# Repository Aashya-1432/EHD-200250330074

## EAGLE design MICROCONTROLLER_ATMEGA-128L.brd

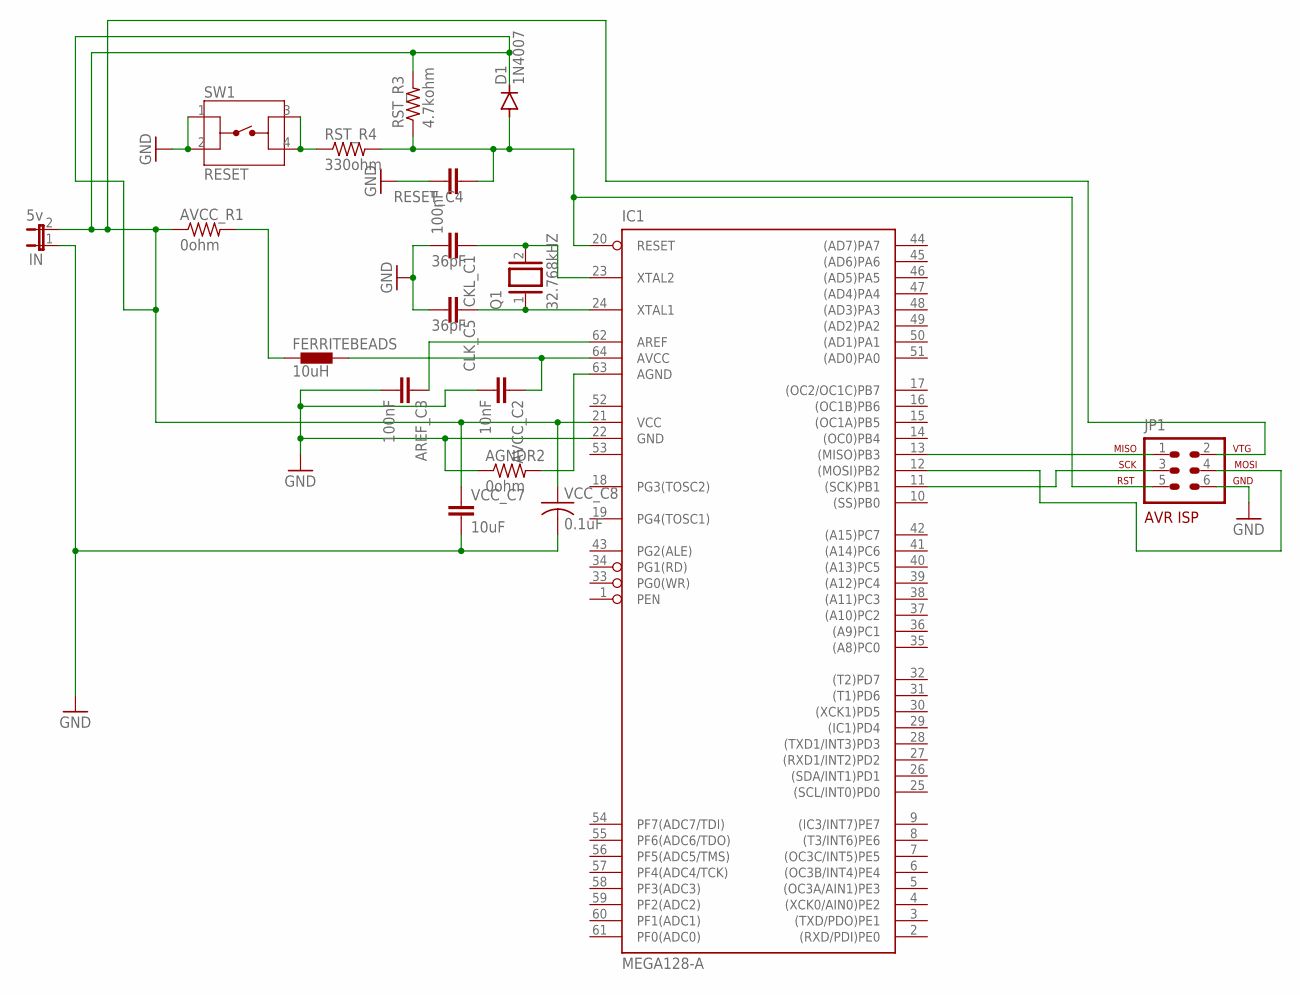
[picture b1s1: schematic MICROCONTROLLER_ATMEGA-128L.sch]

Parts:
AGNDR2: 0ohm; 0204/5
AREF_C3: 100nF; C5B3
AVCC_C2: 10nF; C5B3
AVCC_R1: 0ohm; 0204/5
CKL_C1: 36pF; C5B3
CLK_C5: 36pF; C5B3
D1: 1N4007; DO41-10
FERRITEBEADS: 10uH; 0402
IC1: MEGA128-A; TQFP64
IN: 5v; JP1
JP1: AVR-ISP-6R
Q1: 32.768kHZ; QS
RESET_C4: 100nF; C5B3
RST_R3: 4.7kohm; 0204/5
RST_R4: 330ohm; 0204/5
SW1: RESET; TE_FSM4JSMA
VCC_C7: 10uF; C5B3
VCC_C8: 0.1uF; C0603K

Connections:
GND: AGNDR2.1, AREF_C3.2, AVCC_C2.2, CKL_C1.2, CLK_C5.2, IC1.22 (GND), IN.1, JP1.6, RESET_C4.2, SW1.1, SW1.2, VCC_C7.2, VCC_C8.2
GND1: IC1.53 (GND1)
unnamed: RST_R4.1, SW1.3, SW1.4
unnamed: AVCC_R1.2, FERRITEBEADS.1
unnamed: AGNDR2.2, IC1.63 (AGND)
unnamed: AVCC_C2.1, FERRITEBEADS.2, IC1.64 (AVCC)
unnamed: AREF_C3.1, IC1.62 (AREF)
unnamed: D1.A, IC1.20 (RESET), JP1.5, RESET_C4.1, RST_R3.1, RST_R4.2
unnamed: CKL_C1.1, IC1.23 (XTAL2), Q1.2
unnamed: IC1.13 ((MISO)PB3), JP1.1
unnamed: CLK_C5.1, IC1.24 (XTAL1), Q1.1
unnamed: IC1.11 ((SCK)PB1), JP1.3
unnamed: IC1.12 ((MOSI)PB2), JP1.4
unnamed: AVCC_R1.1, D1.C, IC1.21 (VCC), IN.2, JP1.2, RST_R3.2, VCC_C7.1, VCC_C8.1
VCC1: IC1.52 (VCC1)

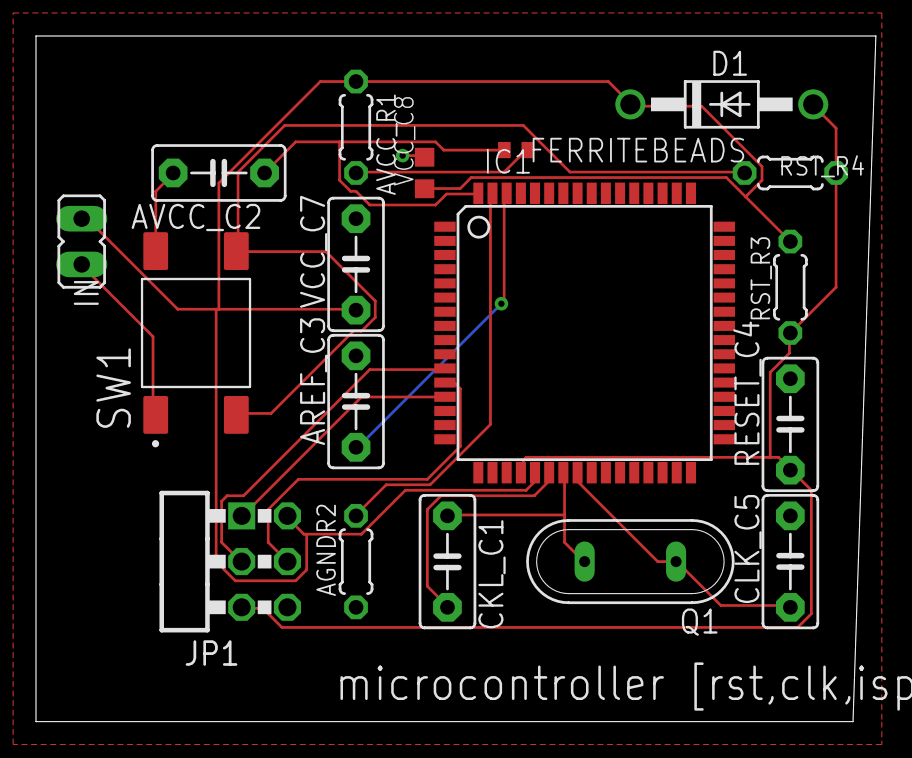
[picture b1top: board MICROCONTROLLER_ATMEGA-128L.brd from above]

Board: 2 copper layers, 46.7 x 38.1 mm, 18 parts (0 on the bottom side), 13 nets.

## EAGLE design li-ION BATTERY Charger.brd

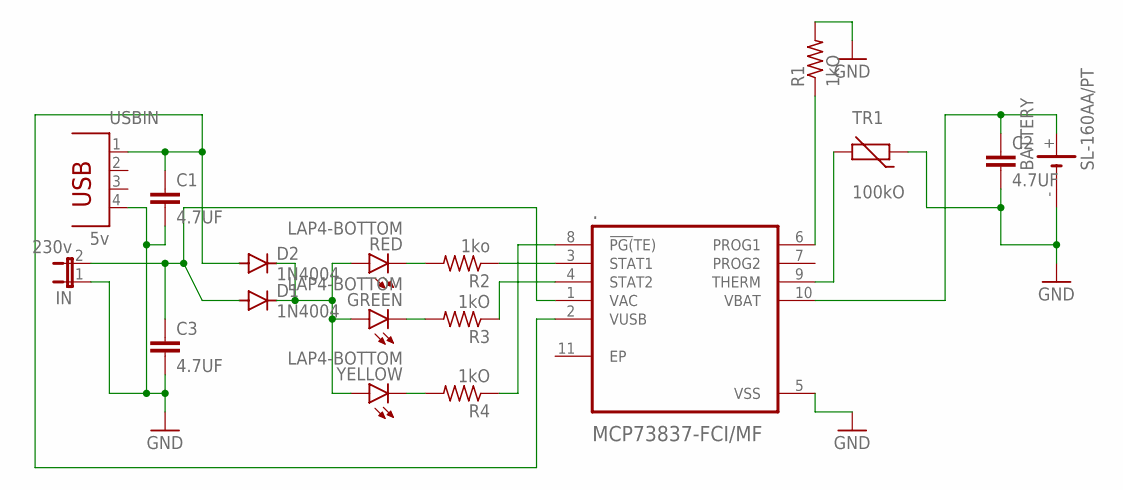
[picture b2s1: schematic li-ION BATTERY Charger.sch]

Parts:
.: MCP73837-FCI/MF; DFN300X300X100-11N
BATTERY: SL-160AA/PT
C1, C2, C3: 4.7UF; C5B2.5
D1, D2: 1N4004; DO41-10
GREEN: LAP4-BOTTOM; P47F-BOTTOM
IN: 230v; JP1
R1, R3, R4: 1kO; 0309/12
R2: 1ko; 0309/12
RED: LAP4-BOTTOM; P47F-BOTTOM
TR1: 100kO; R-7,5
USBIN: 5v; PN87520
YELLOW: LAP4-BOTTOM; P47F-BOTTOM

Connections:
GND: ..5 (VSS), BATTERY.-, C1.2, C2.2, C3.2, IN.1, R1.2, TR1.1, USBIN.4
unnamed: ..3 (STAT1), R2.1
unnamed: ..1 (VAC), C3.1, D1.A, IN.2
unnamed: ..4 (STAT2), R3.1
unnamed: ..10 (VBAT), BATTERY.+, C2.1
unnamed: GREEN.C, R3.2
unnamed: R2.2, RED.C
unnamed: R4.2, YELLOW.C
unnamed: ..8 (!PG(!TE)), R4.1
unnamed: ..9 (THERM), TR1.2
unnamed: ..6 (PROG1), R1.1
unnamed: D1.C, D2.C, GREEN.A, RED.A, YELLOW.A
unnamed: ..2 (VUSB), C1.1, D2.A, USBIN.1

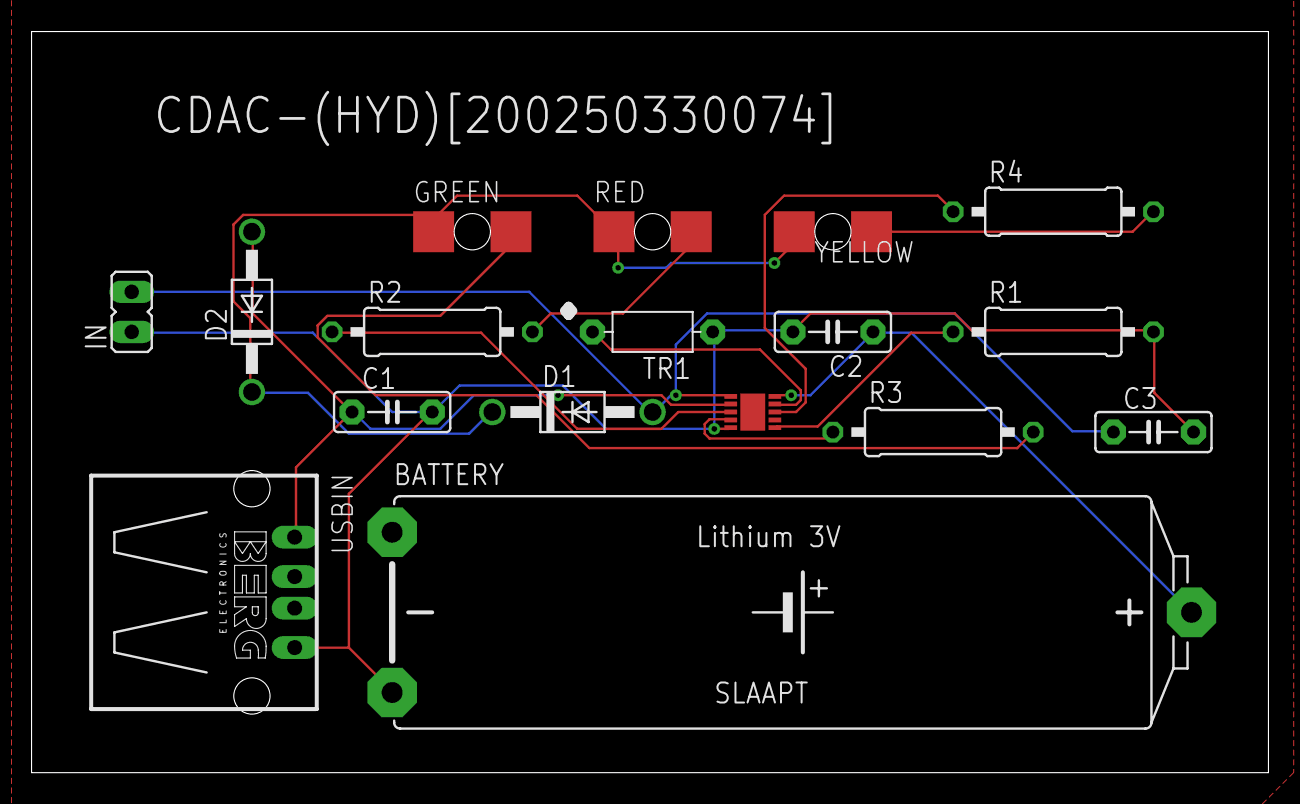
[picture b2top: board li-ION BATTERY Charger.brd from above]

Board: 2 copper layers, 78.4 x 47.0 mm, 17 parts (0 on the bottom side), 13 nets.

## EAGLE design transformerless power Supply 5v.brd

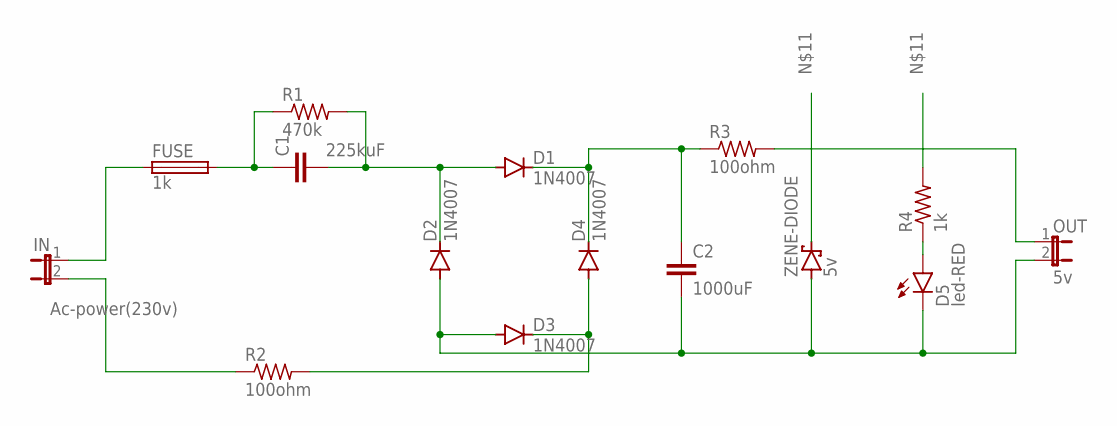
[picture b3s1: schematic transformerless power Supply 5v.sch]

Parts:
C1: 225kuF; C5B3
C2: 1000uF; C5B3
D1, D2, D3, D4: 1N4007; DO41-10
D5: led-RED; SFH482
FUSE: 1k; PICOFUSE
IN: Ac-power(230v); JP1
OUT: 5v; JP1
R1: 470k; 0207/10
R2, R3: 100ohm; 0207/10
R4: 1k; 0207/10
ZENE-DIODE: 5v; C1702-15

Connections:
unnamed: FUSE.1, IN.1
unnamed: C1.1, FUSE.2, R1.1
unnamed: D5.A, R4.1
unnamed: IN.2, R2.1
unnamed: D3.C, D4.A, R2.2
unnamed: C1.2, D1.A, D2.C, R1.2
unnamed: C2.1, D1.C, D4.C, R3.1
unnamed: OUT.1, R3.2
unnamed: C2.2, D2.A, D3.A, D5.K (C), OUT.2, ZENE-DIODE.A
unnamed: R4.2, ZENE-DIODE.C

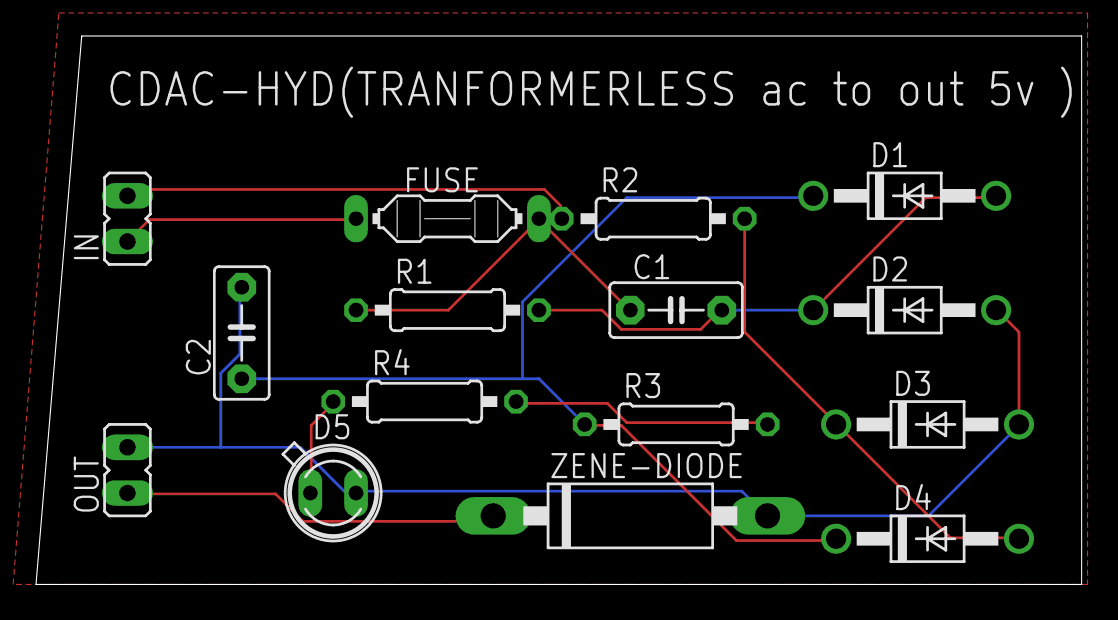
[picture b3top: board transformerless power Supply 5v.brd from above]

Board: 2 copper layers, 58.1 x 30.5 mm, 15 parts (0 on the bottom side), 10 nets.

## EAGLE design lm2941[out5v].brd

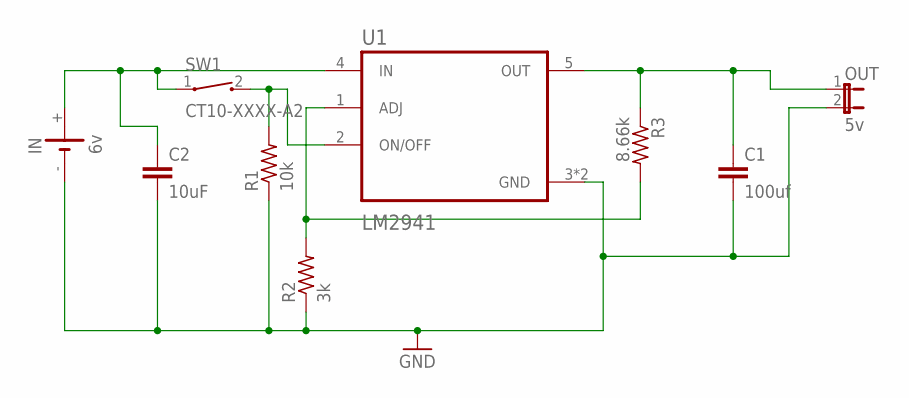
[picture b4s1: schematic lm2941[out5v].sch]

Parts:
C1: 100uf; C5B3
C2: 10uF; C5B3
IN: 6v; SL-160AA/PR
OUT: 5v; JP1
R1: 10k; 0207/10
R2: 3k; 0207/10
R3: 8.66k; 0207/10
SW1: CT10-XXXX-A2
U1: LM2941; VREG_TPS79625KTTR

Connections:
GND: C1.2, C2.2, IN.-, OUT.2, R1.1, R2.1, U1.3 (GND), U1.6 (GND)
unnamed: C2.1, IN.+, SW1.1, U1.4 (IN)
unnamed: R2.2, R3.2, U1.1 (ADJ)
unnamed: R1.2, SW1.2, U1.2 (ON/OFF)
unnamed: C1.1, OUT.1, R3.1, U1.5 (OUT)

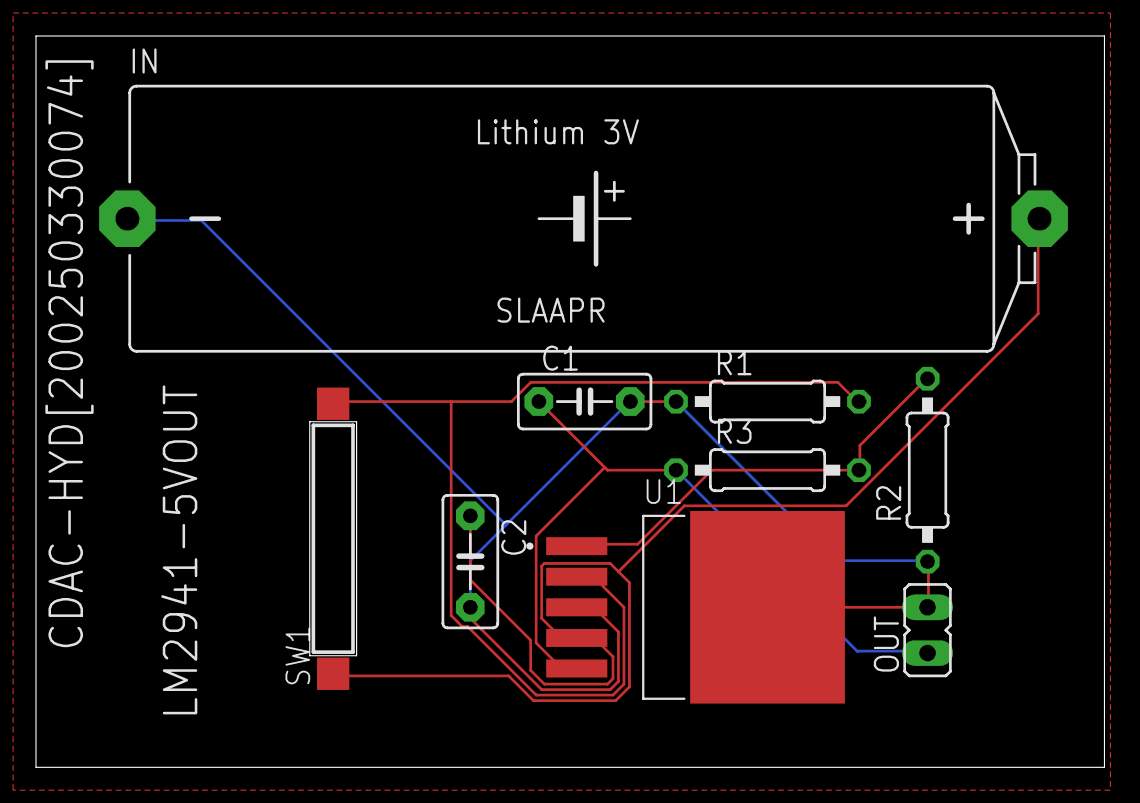
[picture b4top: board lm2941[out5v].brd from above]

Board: 2 copper layers, 59.4 x 40.6 mm, 9 parts (0 on the bottom side), 5 nets.

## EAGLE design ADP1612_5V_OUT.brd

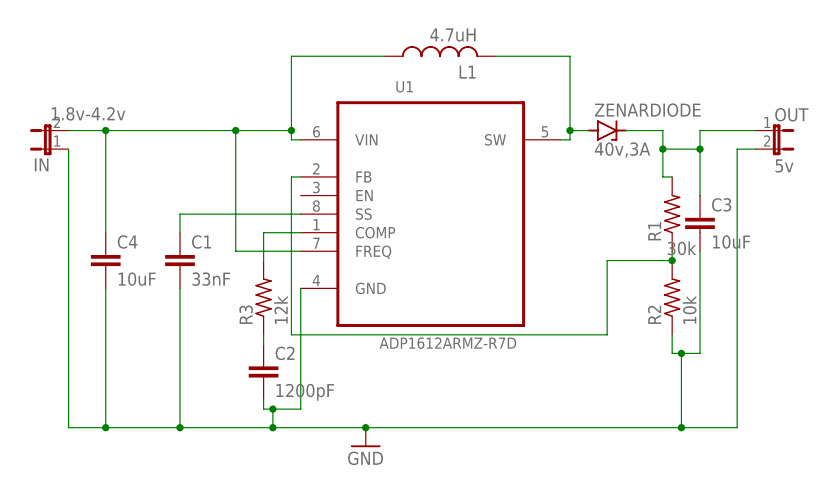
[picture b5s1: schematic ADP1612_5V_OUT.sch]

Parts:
C1: 33nF; C5B3
C2: 1200pF; C5B3
C3, C4: 10uF; C5B3
IN: 1.8v-4.2v; JP1
L1: 4.7uH; 0207/10
OUT: 5v; JP1
R1: 30k; 0207/7
R2: 10k; 0207/7
R3: 12k; 0207/7
U1: ADP1612ARMZ-R7D; SOIC-08
ZENARDIODE: 40v,3A; DO35Z10

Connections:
GND: C1.2, C2.2, C3.2, C4.2, IN.1, OUT.2, R2.1, U1.4 (GND)
unnamed: C4.1, IN.2, L1.1, U1.6 (VIN), U1.7 (FREQ)
unnamed: L1.2, U1.5 (SW), ZENARDIODE.A
unnamed: C3.1, OUT.1, R1.2, ZENARDIODE.C
unnamed: C2.1, R3.1
unnamed: R1.1, R2.2, U1.2 (FB)
unnamed: C1.1, U1.8 (SS)
unnamed: R3.2, U1.1 (COMP)

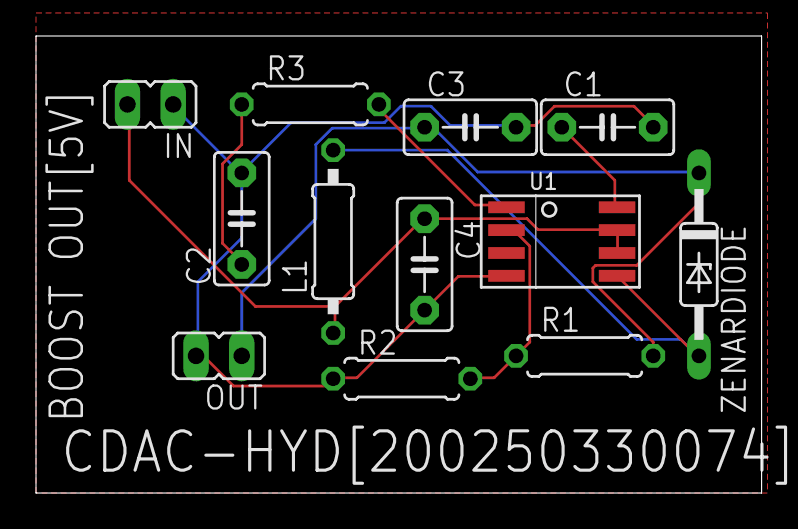
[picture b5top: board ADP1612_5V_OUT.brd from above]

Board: 2 copper layers, 40.3 x 25.4 mm, 12 parts (0 on the bottom side), 8 nets.

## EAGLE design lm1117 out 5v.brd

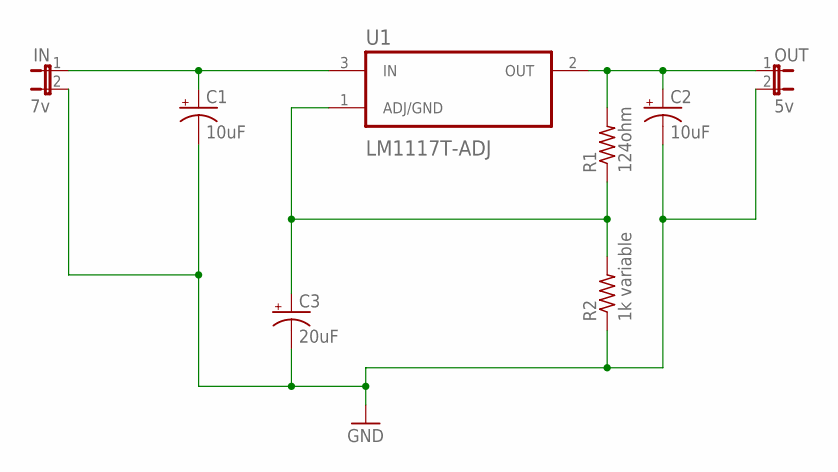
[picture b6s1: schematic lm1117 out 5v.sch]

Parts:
C1, C2: 10uF; CT6032
C3: 20uF; CT6032
IN: 7v; JP1
OUT: 5v; JP1
R1: 124ohm; 0207/7
R2: 1k variable; 0207/7
U1: LM1117T-ADJ; TO254P1054X470X1955-3

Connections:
GND: C1.-, C2.-, C3.-, IN.2, OUT.2, R2.1
unnamed: C1.+, IN.1, U1.3 (IN)
unnamed: C2.+, OUT.1, R1.2, U1.2 (OUT)
unnamed: C3.+, R1.1, R2.2, U1.1 (ADJ/GND)

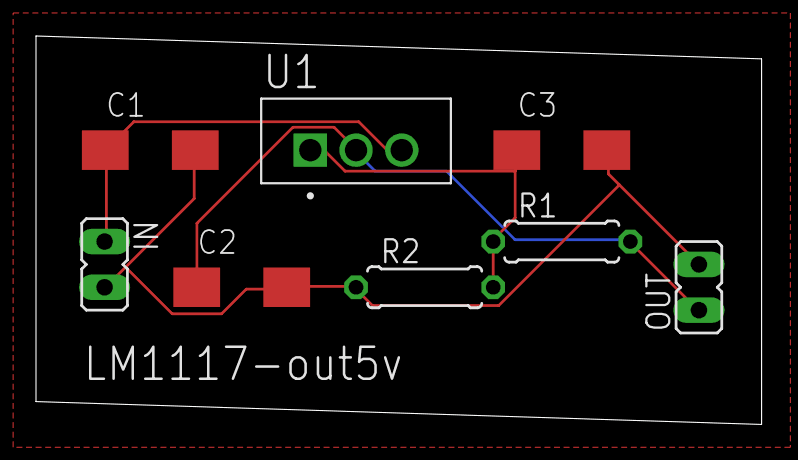
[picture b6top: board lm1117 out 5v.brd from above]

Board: 2 copper layers, 40.3 x 21.6 mm, 8 parts (0 on the bottom side), 4 nets.

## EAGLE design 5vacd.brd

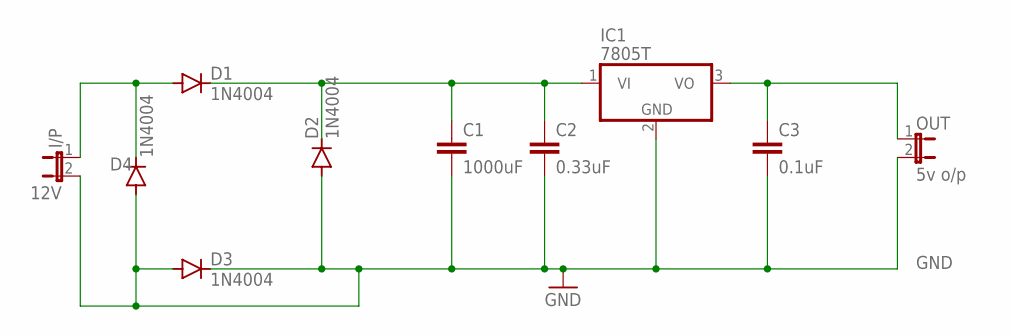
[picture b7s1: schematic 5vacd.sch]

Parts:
C1: 1000uF; C2.5-3
C2: 0.33uF; C2.5-3
C3: 0.1uF; C2.5-3
D1, D2, D3, D4: 1N4004; DO41-10
I/P: 12V; JP1
IC1: 7805T; TO220H
OUT: 5v o/p; JP1

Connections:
GND: C1.2, C2.2, C3.2, D2.A, D3.A, D3.C, D4.A, I/P.2, IC1.2 (GND), OUT.2
unnamed: D1.A, D4.C, I/P.1
unnamed: C1.1, C2.1, D1.C, D2.C, IC1.1 (VI)
unnamed: C3.1, IC1.3 (VO), OUT.1

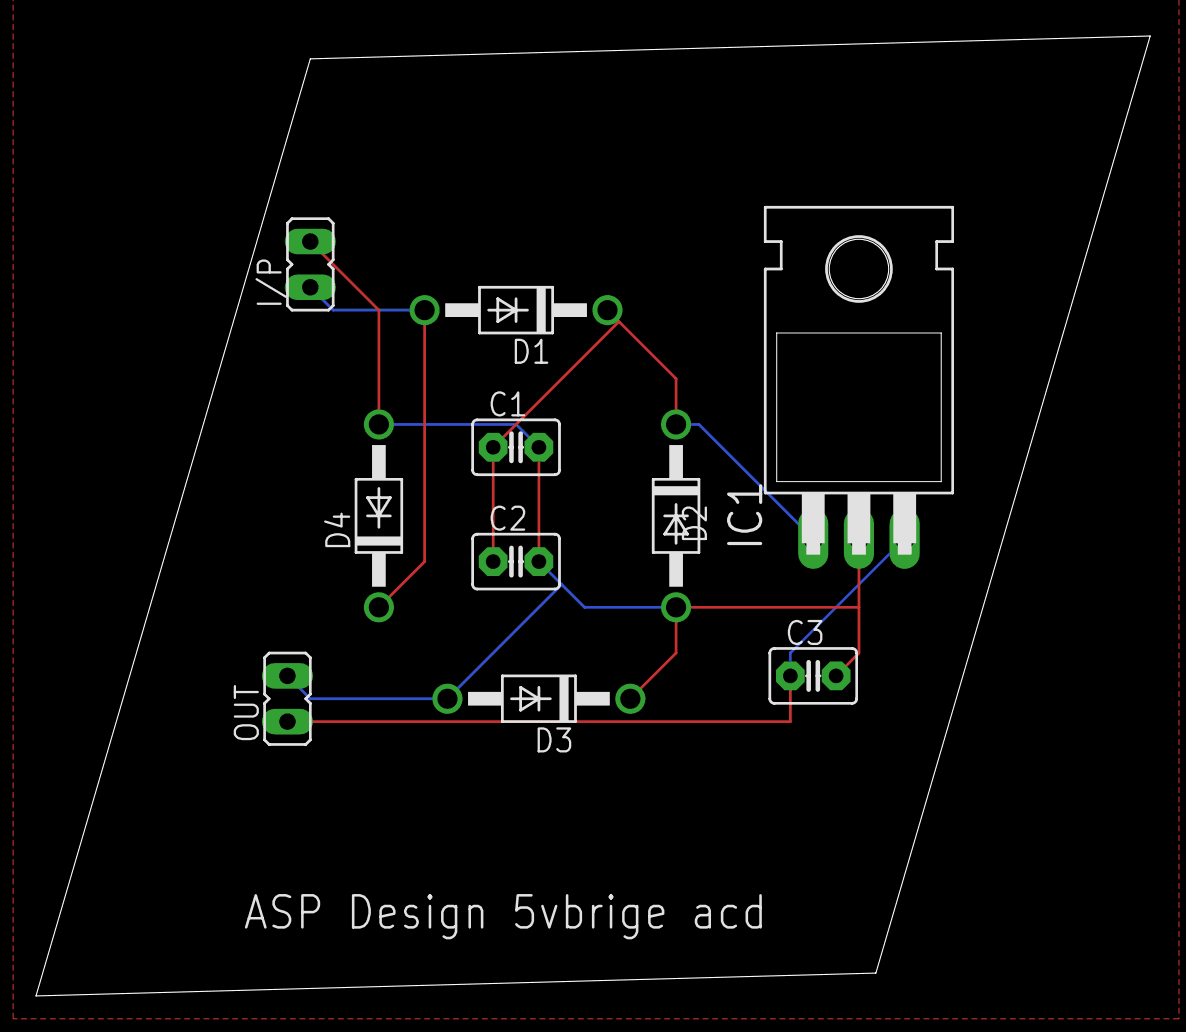
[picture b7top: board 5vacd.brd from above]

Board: 2 copper layers, 61.9 x 53.3 mm, 10 parts (0 on the bottom side), 4 nets.

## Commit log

2020-10-13 Create microcontroller[rst,clk,ips]
